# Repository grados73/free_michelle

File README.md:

# Aquarium controller
>The project, with the working name "free_miechelle", is a response to the lack of market proposals for aquarium control and management devices.

>>Now this project is being developed in another repository. -> https://github.com/grados73/akwa_elektron

## Table of contents
* [General info](#general-info)
* [Screenshots](#screenshots)
* [Technologies](#technologies)
* [HARDWARE](#hardware)
* [Features](#features)
* [Status](#status)
* [Inspiration](#inspiration)
* [Contact](#contact)

## General info
Aquarium hobby has been one of my hobbies for over 10 years, along with cars, sports and electronics. I am a bit of a gadgeteer and like to have everything possible in a smart version, with easy management and monitoring. The same goes for aquariums, I would like to enjoy all the benefits that come with this hobby. Yes, I am a bit lazy. I would like to put in as little effort as possible, while being sure that my fish are well taken care of, even when I am away from home.  But there are no satisfactory solutions on the market to buy and use. All the devices that already exist have either limited capabilities or a technological debt that is heavily visible. Therefore, I decided to make such a device myself. I am currently at the stage of the first prototype, which I assemble using prototype boards. 

## Screenshots
Currently, the device is in a prototype version. It has been assembled on two prototype boards. The next version will have a dedicated PCB.

Short wideo:
https://youtu.be/HiZ6xpy-laI

Currently, the software allows you to control the device and communicate with it through a 2.4" TFT screen, controlled by SPI. All commands are issued via the touch screen available on each of the 8 menu screens. 

## Technologies
Project is created with:
* C,
* HAL for STM32F4,
*
* STM32CubeIDE,
* The Dot Factory v.0.1.4,
* InkScape v.0.92.4,
* Image2Lcd v3.2

## HARDWARE
* 2x Blackpill STM32F411CEU6 
* TFT LCD 2,4″ (240x320px) with ILI9341 controller - SPI
* RTC DS3231 - I2C
* EEPROM memory 1kb - I2C
* BMP280 - I2C
* DS18B20 - 1-WIRE
* Ultrasonic distance sensor - DFRobot SEN0311 - UART
* WS2812b - I2C

## Features
* Menu on TFT Display - DONE
* Touch Interface - DONE
* Relay Control - DONE
* WS2812b LEDs Control  - DONE
* Predefined Activities like feeding or cleaning - DONE
* Display Pressure and Temperature inside and outside the aquarium  - DONE
* Display current day of week, hour and minute and possibility to change them in RTC - DONE
* Measuring the water level in the aquarium - DONE

## To-do list
* Shedules - TODO
* Alarms - TODO
* PCB - TODO
* Watchdog - TODO
* UPS - TODO
* Online access(ESP) - TODO
* Wireless comunitation with sensors - nRF24L01+ - TODO
* Push inormation on telephone - TODO

## Status
Project is in progress and i will develop them to learn ARM and STM32.

## Inspiration
It will be added.

## Contact
Created by https://www.linkedin.com/in/kamil-gradowski-8706991aa - feel free to contact me!
grados73

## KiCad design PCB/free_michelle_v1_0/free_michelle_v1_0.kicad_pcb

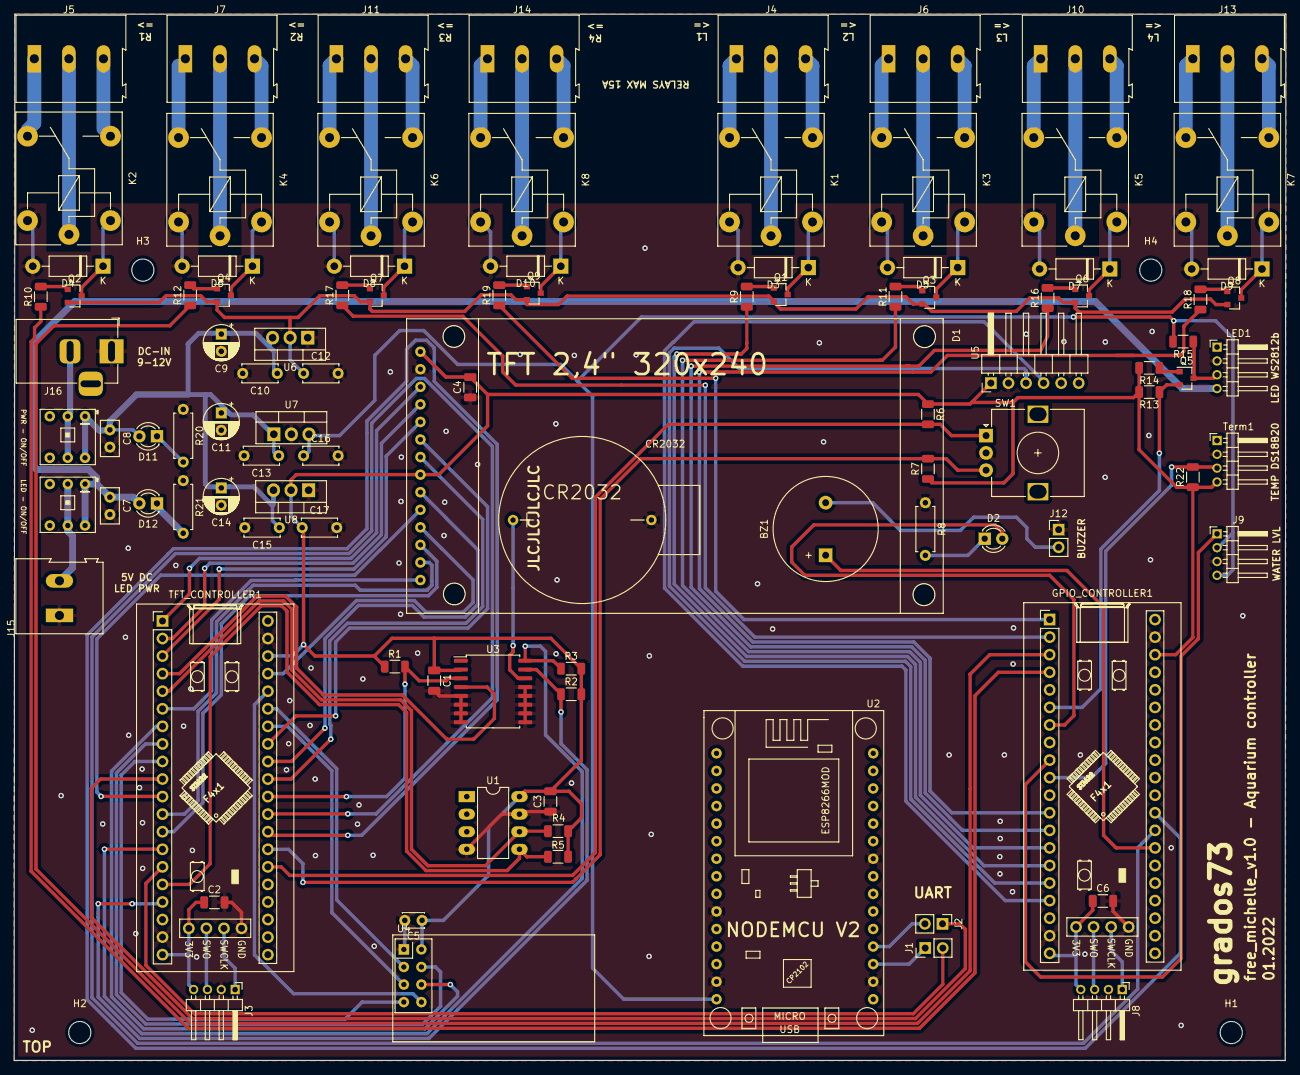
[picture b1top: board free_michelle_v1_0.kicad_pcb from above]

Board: 2 copper layers, 183.9 x 151.3 mm, 105 parts (0 on the bottom side), 105 nets.

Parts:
BZ1: Buzzer; Buzzer_15x7.5RM7.6
C1, C2, C3, C4, C6: 100nF; C_1206_3216Metric
C5: 1uF; C_Disc_D3.0mm_W2.0mm_P2.50mm
C7, C8: 100nF; C_Disc_D5.0mm_W2.5mm_P2.50mm
C9, C11, C14: 47uF; CP_Radial_D5.0mm_P2.50mm
C10, C12, C13, C15, C16, C17: 100nF; C_Disc_D5.0mm_W2.5mm_P5.00mm
CR2032: 3V; CR2032_KOSZYK
D1: TFT_320x240_ILI9341; TFT_2_4_c_240x320_SPI
D2: GREEN_USER_LED; LED_D3.0mm_IRGrey
D3, D4, D5, D6, D7, D8, D9, D10: 1N4148; D_DO-41_SOD81_P10.16mm_Horizontal
D11: RED_LED; LED_D3.0mm
D12: YELLOW_LED; LED_D3.0mm_Clear
GPIO_CONTROLLER1: BlackPill_STM32F4x1_grados73; grados73_BlackPill_STM32F4x1
H1, H2, H3, H4: MountingHole; MountingHole_3.2mm_M3
J1: Zworka_TX; PinHeader_1x02_P2.54mm_Vertical
J2: Zworka_RX; PinHeader_1x02_P2.54mm_Vertical
J3, J8: GROVE_SW; PinHeader_1x04_P2.00mm_Horizontal
J4, J5, J6, J7, J10, J11, J13, J14: ARK; TerminalBlock_Altech_AK300-3_P5.00mm
J9: A02YYUW_GroveCON; PinHeader_1x04_P2.00mm_Horizontal
J12: Zworka_Buzzer; PinHeader_1x02_P2.54mm_Vertical
J15: Gniazdo 5VP DC 5,5x2,5; TerminalBlock_Altech_AK300-2_P5.00mm
J16: Gniazdo 9V DC 5,5x2,5; BarrelJack_Horizontal
K1, K2, K3, K4, K5, K6, K7, K8: FINDER-36.11; Relay_SPDT_Finder_36.11
LED1: WS2812b_GROVE; PinHeader_1x04_P2.00mm_Horizontal
Q1, Q2, Q3, Q4, Q6, Q7, Q8, Q9: MMBT4403_PNP; SOT-23
Q5: BSS138; SOT-23
R1, R6, R7: 10k; R_1206_3216Metric
R2, R3, R13, R14, R15: 4k7; R_1206_3216Metric
R4, R5, R22: 4K7; R_1206_3216Metric
R8: 110; R_Axial_DIN0207_L6.3mm_D2.5mm_P7.62mm_Horizontal
R9, R10, R11, R12, R16, R17, R18, R19: 2.2k; R_1206_3216Metric
R20: 730; R_Axial_DIN0207_L6.3mm_D2.5mm_P7.62mm_Horizontal
R21: 290; R_Axial_DIN0207_L6.3mm_D2.5mm_P7.62mm_Horizontal
SW1: Rotary_Encoder; RotaryEncoder_Alps_EC12E_Vertical_H20mm
SW2, SW3: SW_Push; Switch_BS800L
TFT_CONTROLLER1: BlackPill_STM32F4x1_grados73; grados73_BlackPill_STM32F4x1
Term1: DS18B20_GroveCON; PinHeader_1x04_P2.00mm_Horizontal
U1: EEPROM_24AA01; DIP-8_W7.62mm_LongPads
U2: ESP8266_NodeMCU_v2; NodeMCU_v2_ESP_grados73
U3: DS3231M_RTC; SOIC-16W_7.5x10.3mm_P1.27mm
U4: NRF24L01_Breakout; nRF24L01_Breakout
U5: BMP280; PinHeader_1x06_P2.54mm_Horizontal
U6, U8: LD1117AV33; TO-220-3_Vertical
U7: L7805; TO-220-3_Vertical

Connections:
+3.3VP: C12.1, Q1.2, Q2.2, Q3.2, Q4.2, Q6.2, Q7.2, Q8.2, Q9.2, U6.2
+3V3: C1.1, C2.1, C3.2, C4.2, C5.1, C6.1, C17.1, D1.1, D1.8, GPIO_CONTROLLER1.18, GPIO_CONTROLLER1.40, GPIO_CONTROLLER1.44, J3.4, J8.4, R1.1, R2.2, R3.2, R4.1, R5.1, R6.1, R7.1, R13.2, R14.2, R22.1, TFT_CONTROLLER1.18, TFT_CONTROLLER1.40, TFT_CONTROLLER1.44, Term1.4, U1.8, U3.2, U4.2, U5.1, U8.2
+5V: C16.1, J9.2, J9.4, R15.2, U2.15, U7.3
+5VP: C7.1, D12.2, LED1.4, SW3.1
+9V: C8.1, C9.1, C10.1, C11.1, C13.1, C14.1, C15.1, D11.2, SW2.1, U6.3, U7.1, U8.3
A02YYUW_U6_RX_PA12: GPIO_CONTROLLER1.29, J9.1
BMP_SCL_PB8: GPIO_CONTROLLER1.36, U5.3
BMP_SDA_PB9: GPIO_CONTROLLER1.37, U5.4
Buzzer_PA1: BZ1.1, GPIO_CONTROLLER1.7
DS18B20_1WIRE_PA15: GPIO_CONTROLLER1.30, R22.2, Term1.3
DS3231_IRQ_PA4: R1.2, TFT_CONTROLLER1.10, U3.3
DS3231_RST_PB15: TFT_CONTROLLER1.24, U3.4
DS3231_SCL_PB6: R3.1, TFT_CONTROLLER1.34, U3.16
DS3231_SDA_PB9: R2.1, TFT_CONTROLLER1.37, U3.15
EEPROM_SCL_PA8: R4.2, TFT_CONTROLLER1.25, U1.6
EEPROM_SDA_PB8: R5.2, TFT_CONTROLLER1.36, U1.5
ENC_CLK_PA1: R7.2, SW1.B, TFT_CONTROLLER1.7
ENC_DT_PA0: R6.2, SW1.A, TFT_CONTROLLER1.6
ESP_RX_TX_STM__U1_PA15: J2.1, TFT_CONTROLLER1.30
ESP_TX_RX_STM__U1_PB7: J1.2, TFT_CONTROLLER1.35
GND: C1.2, C2.2, C3.1, C4.1, C5.2, C6.2, C7.2, C8.2, C9.2, C10.2, C11.2, C12.2, C13.2, C14.2, C15.2, C16.2, C17.2, CR2032.2, D1.2, D3.2, D4.2, D5.2, D6.2, D7.2, D8.2, D9.2, D10.2, GPIO_CONTROLLER1.19, GPIO_CONTROLLER1.39, GPIO_CONTROLLER1.41, J3.2, J8.2, J9.3, J12.1, J15.1, J16.1, K1.A2, K2.A2, K3.A2, K4.A2, K5.A2, K6.A2, K7.A2, K8.A2, LED1.2, R8.1, R20.1, R21.1, SW1.C, TFT_CONTROLLER1.19, TFT_CONTROLLER1.39, TFT_CONTROLLER1.41, Term1.2, U1.4, U1.7, U2.10, U2.14, U2.22, U2.29, U3.5, U3.6, U3.7, U3.8, U3.9, U3.10, U3.11, U3.12, U3.13, U4.1, U5.2, U6.1, U7.2, U8.1
LIGHT1_PB7: GPIO_CONTROLLER1.35, R9.1
LIGHT2_PB6: GPIO_CONTROLLER1.34, R11.1
LIGHT3_PB5: GPIO_CONTROLLER1.33, R16.1
LIGHT4_PB4: GPIO_CONTROLLER1.32, R18.1
unnamed: BZ1.2, J12.2
unnamed: CR2032.1, U3.14
unnamed: D2.1, R8.2
unnamed: D3.1, K1.A1, Q1.3
unnamed: D4.1, K2.A1, Q2.3
unnamed: D5.1, K3.A1, Q3.3
unnamed: D6.1, K4.A1, Q4.3
unnamed: D7.1, K5.A1, Q6.3
unnamed: D8.1, K6.A1, Q7.3
unnamed: D9.1, K7.A1, Q8.3
unnamed: D10.1, K8.A1, Q9.3
unnamed: D11.1, R20.2
unnamed: D12.1, R21.2
unnamed: GPIO_CONTROLLER1.8, TFT_CONTROLLER1.9
unnamed: GPIO_CONTROLLER1.9, TFT_CONTROLLER1.8
unnamed: GPIO_CONTROLLER1.42, J8.1
unnamed: GPIO_CONTROLLER1.43, J8.3
unnamed: J1.1, U2.28
unnamed: J2.2, U2.27
unnamed: J3.1, TFT_CONTROLLER1.42
unnamed: J3.3, TFT_CONTROLLER1.43
unnamed: J4.1, K1.12
unnamed: J4.2, K1.11
unnamed: J4.3, K1.14
unnamed: J5.1, K2.12
unnamed: J5.2, K2.11
unnamed: J5.3, K2.14
unnamed: J6.1, K3.12
unnamed: J6.2, K3.11
unnamed: J6.3, K3.14
unnamed: J7.1, K4.12
unnamed: J7.2, K4.11
unnamed: J7.3, K4.14
unnamed: J10.1, K5.12
unnamed: J10.2, K5.11
unnamed: J10.3, K5.14
unnamed: J11.1, K6.12
unnamed: J11.2, K6.11
unnamed: J11.3, K6.14
unnamed: J13.1, K7.12
unnamed: J13.2, K7.11
unnamed: J13.3, K7.14
unnamed: J14.1, K8.12
unnamed: J14.2, K8.11
unnamed: J14.3, K8.14
unnamed: J15.2, SW3.2
unnamed: J16.2, SW2.2
unnamed: LED1.3, Q5.3, R15.1
unnamed: Q1.1, R9.2
unnamed: Q2.1, R10.2
unnamed: Q3.1, R11.2
unnamed: Q4.1, R12.2
unnamed: Q5.1, R14.1
unnamed: Q6.1, R16.2
unnamed: Q7.1, R17.2
unnamed: Q8.1, R18.2
unnamed: Q9.1, R19.2
RELAY1_PB15: GPIO_CONTROLLER1.24, R10.1
RELAY2_PB14: GPIO_CONTROLLER1.23, R12.1
RELAY3_PB13: GPIO_CONTROLLER1.22, R17.1
RELAY4_PB12: GPIO_CONTROLLER1.21, R19.1
TFT_CS_PB12: D1.3, TFT_CONTROLLER1.21
TFT_DC_PB14: D1.5, TFT_CONTROLLER1.23
TFT_MISO_PA6: D1.9, TFT_CONTROLLER1.12
TFT_MOSI_PA7: D1.6, TFT_CONTROLLER1.13
TFT_RST_PB13: D1.4, TFT_CONTROLLER1.22
TFT_SCK_PA5: D1.7, TFT_CONTROLLER1.11
T_TFT_CS_PB10: D1.11, TFT_CONTROLLER1.17
T_TFT_IRQ_PA9: D1.14, TFT_CONTROLLER1.26
T_TFT_MISO_PB4: D1.13, TFT_CONTROLLER1.32
T_TFT_MOSI_PB5: D1.12, TFT_CONTROLLER1.33
T_TFT_SCK_PB3: D1.10, TFT_CONTROLLER1.31
USER_LED_PA10: D2.2, GPIO_CONTROLLER1.27
WS2812b_PA9: GPIO_CONTROLLER1.26, Q5.2, R13.1
nRF24_CE_PB1: TFT_CONTROLLER1.15, U4.3
nRF24_CSN_PA11: TFT_CONTROLLER1.28, U4.4
nRF24_IRQ_PB2: TFT_CONTROLLER1.16, U4.8
nRF24_MISO_PA12: TFT_CONTROLLER1.29, U4.7
nRF24_MOSI_PA10: TFT_CONTROLLER1.27, U4.6
nRF24_SCK_PB0: TFT_CONTROLLER1.14, U4.5

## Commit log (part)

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2021-06-08 Dodany pusty projekt płytki do sterowania wyświetlaczem
2021-06-08 Próbny program z blinkiem diodą działa, zegary ustawione na 80MHz
2021-06-08 Dodane biblioteki do obsługi wyświetlacza, działa czyszczenie wyświetlacza
2021-06-10 Działa pisanie, polskie czcionki, czyszczenie
2021-06-10 Dodana tablica z logo 240x140pix w pliku logo.h
2021-06-10 Dodany szablon inicjalizacji i szablon okna aktualnych parametrów
2021-07-07 dodany plik do parsowania i wstępne stany kontrolera
2021-07-07 poprawiona nazwa funkcji w functions.c
2021-07-07 dodane funkcje do parsowania różnych stanów
2021-07-08 Poprawione błędy dotyczące nazw funkcji
2021-07-20 dodany program controlera
2021-07-20 Dodany zegar z RCC Crystal Ceramic i 100Mhz taktowanie
2021-07-20 Dodana obsługa i2c w CubeMX
2021-07-20 Czyta temperature i wilgotnosc zapisuje je do zmiennych Temp i Pressure, trzeba zrobić to w obsłudze przerwania
2021-09-06 Poprawiona synchronizacja
2021-09-06 Pomiar ciśnienia i temperatury przeniesiony do funkcji obsługi przerwania
2021-09-15 porzucona wersja ze względu na problem z targetem
2021-09-15 Przeimportowany projekt z wersji 02 - działa pomiar temp i pressure w while
2021-09-15 aktualizacja opisu
2021-09-16 Przeniesiony pomiar Temp i Ciśnienia do przerwania od TIM10
2021-10-14 Dodane kości z STMars dotyczące komunikacji
2021-10-14 Dodane inicjalizacje i wywołania funkcji transmisji w mainie
2021-10-14 Dodane UartIrqHandler i DmaReceiveIrqHandler do _it.c
2021-10-14 Dodany prototyp unii do rozszyfrowywania pakietów przychodzących
2021-10-14 Poprawiony prototyp danych w unii.
2021-10-15 Dodana wstępna funkcja parsowania po Message_type i stworzone funkcje typu Routine
2021-11-01 Poparwiony define od ramki i klamry
2021-11-02 powrot do wersji z prostym parsowaniem, bez uzycia interfejsu komunikacyjnego
2021-11-02 Dziala parsowanie - zdalne wlaczanie i wylaczanie diody w uC!
2021-11-03 Dodane parsowanie do polecenia dot. przekaznikow
2021-11-03 Dodane parsowanie do komendy podaj temperature
2021-11-03 Dodane parsowanie do komendy podaj cisnienie
2021-11-03 wszystkie parsowania dzialaja, uprzatniety plik parser.c
2021-11-03 Dziala juz odpowiedz na zapytanie dotyczace temperatury i cisnienia
2021-11-03 Dodana obsluga przekaznikow na polecenia z UARTA
2021-11-03 Migracja do nowej wersji Cube i dodanie kosci do uarta i parsowania
2021-11-04 dodane definicje bledow komunikacji
2021-11-04 dodane prototypy funkcji parsowania odpowiedzi
2021-11-04 Dodane wartosci bledow
2021-11-08 Dodane komentarze naglowkowe i usuniety plik motion.c - pozostalosc z STMars-a
2021-11-24 Zmieniono funkcje rysowania na szybsza
2021-11-24 Dodane rzutowanie argumentu na wskaźnik na char do funkcji sprintf()
2021-11-25 Controler cyklicznie wysyła informację o aktualnych parametrach środowiskowych
2021-11-25 Cykliczne podawanie parametrow zmienione na obsluge przez funkcje
2021-11-25 Dziala parsowanie temperatury od drugiego uC i wyswietlanie
2021-11-25 Dodana obsluga parsowania i wyswietlanie cisnienia
2021-11-26 Dodany prototyp projektu do dodania modułu dotykowego
2021-11-29 Dziala dotyk, pokazuje polozenie X i Y pkt dotkniecia
2021-11-29 Dodany plik z prototypem maszyny stanow do obslugi menuTFT
2021-11-30 Poprawiona funkcja showCurrentParameters
2021-11-30 Dodana czcionka arial_11 z polskimi znakami
2021-11-30 Polozenie parametrow w ekranie parametry przeniesione do #definow
2021-11-30 Dziala przelaczanie pomiedzy parametrami a swiatlami i switchami
2021-11-30 Dodane przejscie pomiedzy 3 ekranami. TODO: naprawa podwojnych klikniec
2021-11-30 Naprawiona usterka z podwojnym przelaczaniem menu
2021-12-03 Dodane definy z pozycja stringow na panelu kontrolnym
2021-12-03 Dodane definy z pozycją stringów w showLightsControlPanel
2021-12-03 Dodano definy z polozeniem, wymiarami i kolorami przyciskow od switchow i swiatel
2021-12-03 Dodane warunki nacisniecia na przycisk do zmiany przekaznika / swiatla
2021-12-05 Poprawione miejsca okienek do zmiany stanu przyciskow
2021-12-05 Dodana funkcja wysylajaca polecenia do drugiego uC
2021-12-06 Dodane warunki rysowania przyciskow
2021-12-06 Dziala sterowanie przekaznikami z wyswietlacza drugiego uC!
2021-12-06 Dodane sterowanie swiatlami, poprawione czcionki i kolory
2021-12-07 Poprawiona wartosc zwracana funkcji - usuniety blad kompilacji
2021-12-07 Dodana funkcja realizujaca zmiane swiatel
2021-12-07 Poprawione wlaczanie 4 swiatla - usuniecie bledu
2021-12-08 Dziala RTC, bez zmiany godzin
2021-12-08 Dziala w pelnie RTC, wraz z interfejsem do zmiany godziny
2021-12-09 Dodany przycisk do przejscia na ekran aktywnosci z panelu sterowania
2021-12-09 Dodana funkcja rysujaca ekran do sterowania predefiniowanymi aktywnosciami
2021-12-09 Dodana funkcja do obslugi wcisniecia przycisku od predefiniowanych aktywnosci
2021-12-09 Dodana osbluga wciscniecia predefined activity i wylaczania activity po czasie
2021-12-09 Posprzątany plik, poprawione komentarze
2021-12-09 dodana funckaj predefiniowanych aktywnosci
2021-12-10 Zmieniony sposob zapytan o stan przekaznikow - do sprawdzenia
2021-12-10 Posprzątane w plikach wykonawczych, poprawione komentarze
2021-12-13 Zmiana trybu pracy RTC na fast mode i zmiana komunikacji z RTC na I2C po DMA
2021-12-13 Dodana obsluga temp na ds18b20, zmieniona funkcja wysyłania katualnej temp - ATEMP
2021-12-13 Dodane parsowanie i wyswietlanie temperatury wewnatrz z ds18b20
2021-12-13 Dodana funkcjonalnosc - czytanie realnego stanu przyciskow i swiatel z drugiego uC!
2021-12-13 Przywrocono systematyczna aktualizacje parametrow, ujednolicono potwierdzenia wykonania
2021-12-17 Dodana prosta biblioteka do oblugi ds18b20 z uzyciem DMA
2021-12-18 Dodana bardziej zaawansowana biblioteka do obslugi ws2812b i parsowanie komend dot LED WS
2021-12-18 Dodanyekran do sterowania diodami WS2812b i funckja go wysująca
2021-12-18 Dodany szzkielet funkcji do obslugi dotyku w panelu sterowania ledami
2021-12-18 Dodane komendy do sterowania diodami WS2812b
2021-12-18 Poprawiono rysowanie w panelu WS2812b
2021-12-20 Poprawiono na wersję z pojedynczym wysylaniem komend - mozliwe po ogarnieciu zasilania
2021-12-21 Dodane I2C3 do obslugi EEPROMu, TOUCH_IRQ przeniesione z PA8 na PA9
2021-12-21 Dodana biblioteka do zapisu i odczytu z pamięci EEPROM
2021-12-22 Dodane definicje do adresow w pamieci EEPROM
2021-12-22 Dodane czytanie i zapisywanie ilosci led do pamieci EEPROM
2021-12-22 Dodane uaktualniania informacji w EEPROM o aktualnym stanie przelacznikow przy zmianie ich stanu
2021-12-22 Hal Delay w inicjalizacji zmieniono na stale odcinki czasu, obejmujace czas inicjalizacji
2021-12-22 Dodane przywracanie stanu swiatel sprzed wylaczenia zasilania z pamieci EEPROM
2021-12-22 Zwiekszona dlugosc bufora danych do USARTA, żeby pomieściła to co się wysyła przy inicjalizacji
2021-12-22 zmieniono sposob inicjalizacji - wysyla komendy w paczkach, zeby nie przepelnic bufora
2021-12-22 Poprawiona funkcja inicjalizacji
2021-12-23 Dodane prototypy funkcji do rysowania ekranu do ustawiania harmonogramow
2021-12-23 Dodane prototypy funkcji do poruszania sie po menu dot harmonogramow
2021-12-23 Dodano UART6 do komunikacji z czujnikiem odległości
2021-12-23 Dodana mozliwosc zmieniania ilosci diod, todo, poprawic dzialanie 3 pierwszych
2021-12-23 Poprawiony blad ze zmiana stanu przycisku od aktywnosci - karmienie
2021-12-23 Poprawione rysowanie funkcji do rysowania ekranu CLOCK
2021-12-27 Dodany prototyp funkcji do czytania odleglosci - wg godbolta czyta cyfry 0-9, trzeba dodac obsluge A-F
2021-12-28 Wersja parsowania odleglosci do sprawdzenia - wg godbolta dziala dla liczb > 9
2021-12-28 Mam dane z czujnika odleglosci w tabeli
2021-12-28 Liczy odleglosc do przeszkody i wysyla ja, ale jest problem z odswiezaniem tej wielkosci
2021-12-29 Dodane dwa rozwiazania naprawienia problemu odswiezania uarta do sprawdzenia
2021-12-30 Usprawniona sekcja inicjalizacji, posprzątane komentarze
2021-12-31 Update README.md
    Added used technologies
2021-12-31 Update README.md
    Update general info about project target.
2021-12-31 Update README.md
    Add DONE features.
2021-12-31 Naprawiony blad cyklicznego pomiaru odleglosci od lustra wody
2022-01-02 Dodana funkcja parsowania poziomu wody i wyswietlania go
2022-01-02 Dodana funckja rysujaca panele od harmonogramow
2022-01-03 Dodane prototypy do czytania danych o godz, min, dzien, przekaznik z eeprom i wyswietlania przy rysowaniu ekranu harmonogramu
2022-01-03 Dodane funkcje czytajajace godzine i minute ON/OFF w harmonogramach z eepromu
2022-01-03 dodane zmienianie godziny i minuty wlaczenia w shedule1
2022-01-03 dodane zmienianie godziny i minuty ON i OO w shedule 1 i shedule 2
2022-01-03 zmienianie godzin ON i OFF w shedule 1 i 2 dziala z zapisywaniem i czytaniem tej godziny z EEPROM
2022-01-04 Dodane prototypy funkcji do czytania i zapisu dnia i przełączników których tyczą dane harmonogramy
2022-01-04 Dodany const coretness w funkcjach do EEPROMU
2022-01-05 Dziala zmiania stanu dni tygodnia na ekranie w harmonogramie 1
2022-01-05 Dodane zapis do i czytanie z EEPROMu zapamietanych dni do 1 harmonogramu
2022-01-05 Dodane zapis do i czytanie z EEPROMu zapamietanych dni do 2 harmonogramu
2022-01-05 Funkcja EEPROM_ScheduleDayInWeekRead poprawiona na bardziej czytelna i optymalna
2022-01-05 Dodane funckje do czytania z EEPROMu i przywracania zapisanego stanu przekaznikow i swiatel
2022-01-05 Dodana funkcja do zapisu do EEPROMu dni, ktore dotycza dane harmonogramy, funkcje od ustalania harmonogramow kompletne
2022-01-05 Add file with photo
2022-01-05 Added device view in v0.1
2022-01-05 Update REAMDE.MD
    Added photos.
2022-01-05 Update Readme - added hardware
2022-01-05 Update README.md - Update To-do list
2022-01-05 Added wideo
2022-01-06 Dodana obsługa błędów w Error_Handler(), poprawione komentarze
2022-01-06 Dodana funkcja do czytania wszystkich informacji o harmonogramach z EEPROMu
2022-01-06 Dodanie funkcji czytania info o harmonogramach przy inicjalizacji systemu
2022-01-06 Obsluga wcisniecia przyciskow od przekaznikow i swiatel przeniesiona do funkcji dla wiekszej czytelnosci
2022-01-06 Obsluga zmiany godzin, zmiany WS, zmiany predefiniowanej aktywnosci przeniesiona do funkcji
2022-01-07 Dodany plik z schematem Układu
2022-01-09 Dodany nowy schemat, naprawiony blad z symbolem f411
2022-01-09 Dodana własna biblioteka symboli
2022-01-09 Dodane 2 STM32F411 i polaczenie ich po UART
2022-01-09 Dodany symbol wyswietlacza TFT 2,4 240x320 ze sterownikiem ILI9341
2022-01-09 Dodano polaczenia pomiedzy uC a TFT
2022-01-09 Dodany DS3231 i podłączony
2022-01-09 Dodane zapomniane rezystory podciągające dla SCL i SDA
2022-01-10 Dodany do schematu element EEPROM 24AA01
2022-01-10 Dodany L7805
2022-01-10 Dodany LD1117V33
2022-01-10 Dodane zasialnie i zlacza do programwoania
2022-01-10 Dodane WS2812b
2022-01-10 Poprawione zapomniane polaczenie led WS do uC
2022-01-11 Dodane przekazniki z tranzystorami kluczującymi
2022-01-11 Dodao i podlaczona nRF24
2022-01-11 Dodane opisy i podział bloków na schemacie
2022-01-12 Dosane ESP do schematu
2022-01-12 Dosane przelaczniki wlaczania zasilania i zlacza do schematu
2022-01-13 Dodany Buzzer
2022-01-13 Poprzypisywane footprinty do glownych urzadzen
2022-01-13 Powybierane wszystkie obudowy i poprzypisywane footprinty
2022-01-14 Ulozone wstepnie elementy na PCB
2022-01-14 Zmienione zlacze dla WS2812b i dodany rezystor filtrujący napięcie
2022-01-15 Poprawki po rozmowie z Mackiem umieszczone na schemacie
2022-01-15 Wykonane polaczenia dla TFT uC i zasilanie
2022-01-15 Wykonane wszystkie polaczenia sygnalowe i zasilania, przed wylaniem masy
2022-01-15 Wylano pola masy na obu stronach PCB
2022-01-15 Dodane napisy i otwory montarzowe pod TFT
2022-01-18 Gotowa płytka przed generacją gerberow
2022-01-18 Dodane gerbery dla jlc
2022-01-18 Poprawione warstwy z napisami
2022-01-18 Wygenerowane gerbery dla jlcpcb z poprawionymi warstwami napisów
2022-02-24 DOdane Readme
2022-02-24 Dodany pdf z konfiguracja projektu.
    Dodano wygenerowany plik pdf zawierajacy informacje o projekcie.
2022-02-24 Dodano plik .gitignore
